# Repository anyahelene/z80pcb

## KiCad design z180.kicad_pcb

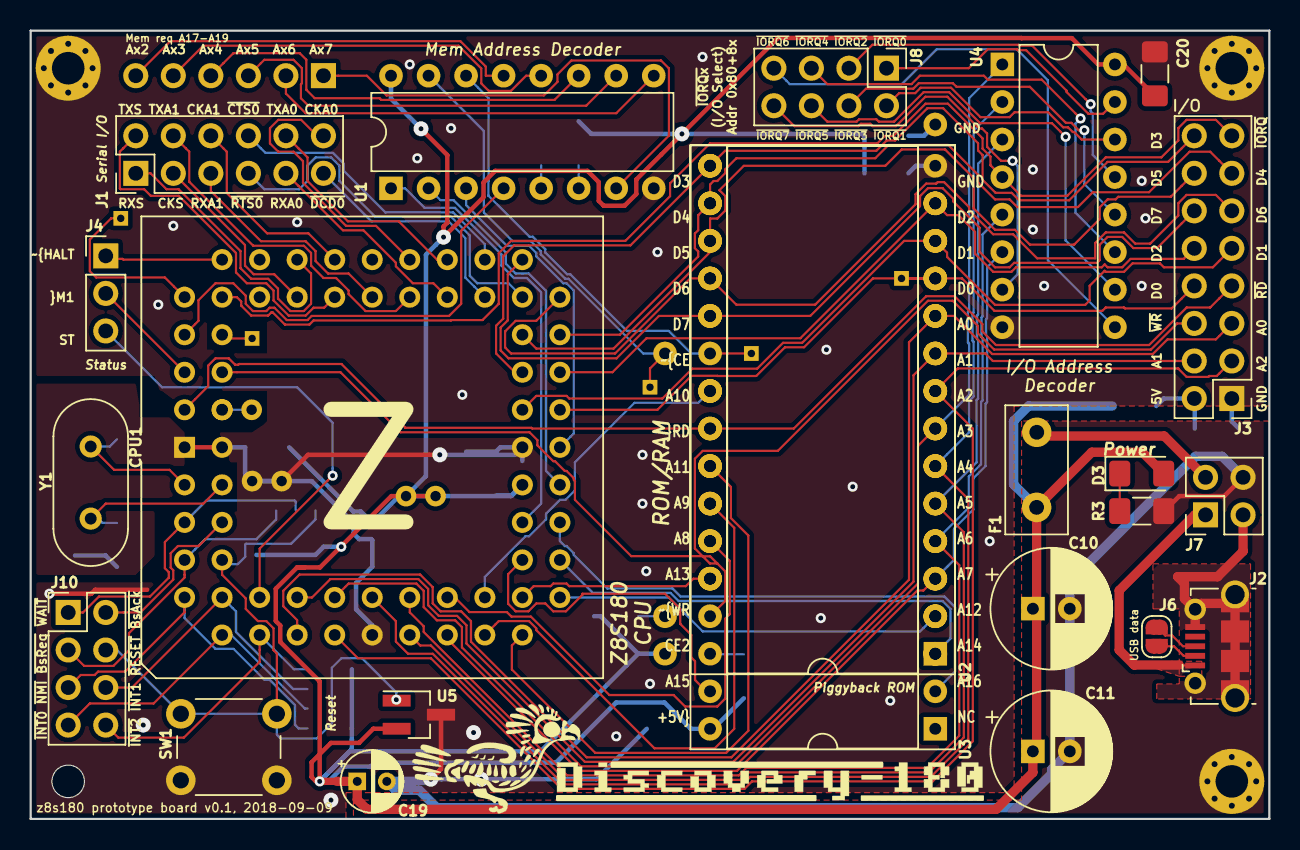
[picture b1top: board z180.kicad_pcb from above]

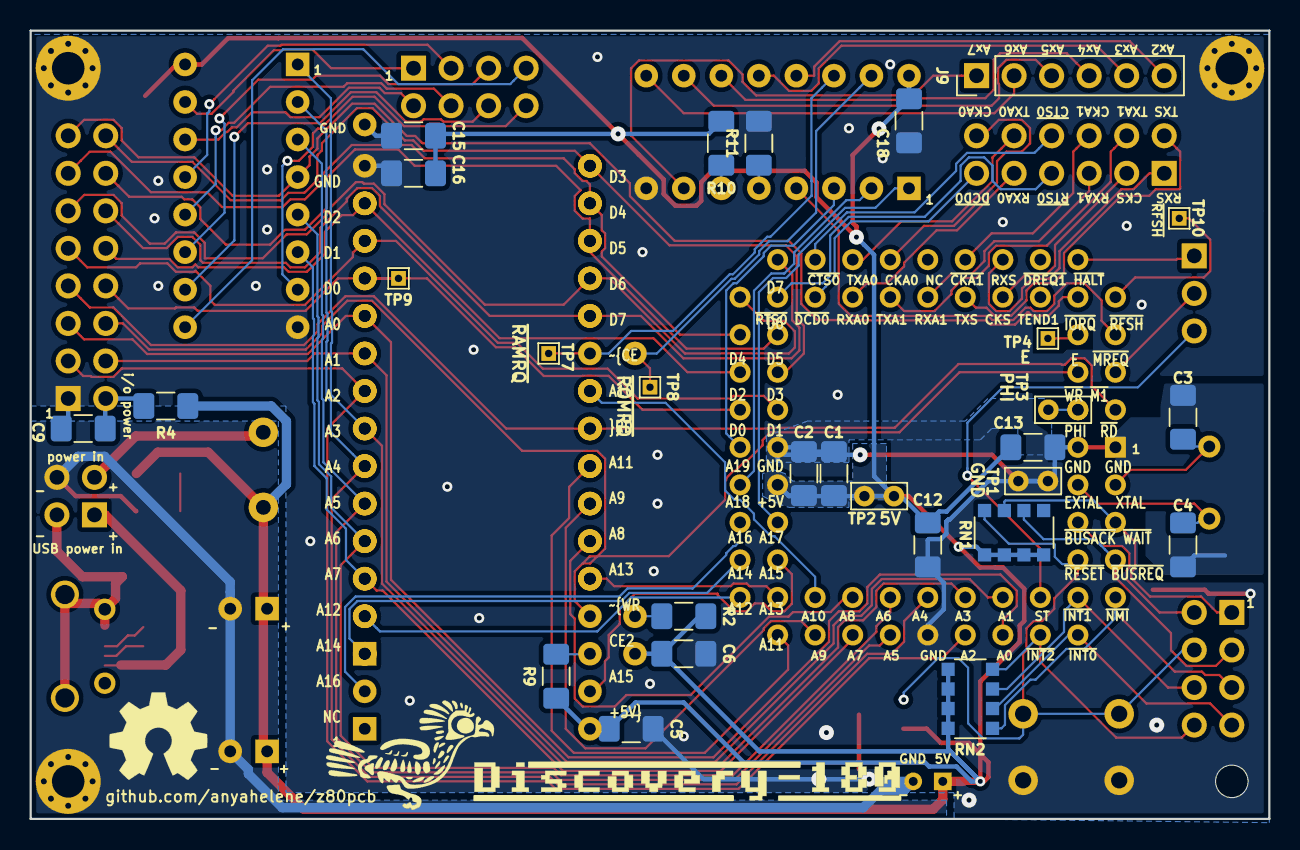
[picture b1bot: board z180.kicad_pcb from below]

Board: 2 copper layers, 83.8 x 53.3 mm, 62 parts (32 on the bottom side), 91 nets.

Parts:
C1, C5, C6, C9, C12, C13, C15, C16, C18, C20: 0.1µF; C_1206_3216Metric_Pad1.42x1.75mm_HandSolder
C2: 0.01µF; C_1206_3216Metric_Pad1.42x1.75mm_HandSolder
C3, C4: 22pF; C_1206_3216Metric_Pad1.42x1.75mm_HandSolder
C10: 10µF; CP_Radial_D8.0mm_P2.50mm
C11: 1µF; CP_Radial_D8.0mm_P2.50mm
C19: 1µF; CP_Radial_D4.0mm_P2.00mm
CPU1: Z8S180; PLCC-68_THT-Socket
D3: PWR_LED; LED_1206_3216Metric_Pad1.42x1.75mm_HandSolder
F1: 650mA; Fuse_Littlefuse_395Series
J1: SERIAL_IO; PinHeader_2x06_P2.54mm_Vertical
J2: USB Micro-B 105017; USB_Micro-B_Molex-105017-0001
J3: zdbus; PinHeader_2x08_P2.54mm_Vertical
J4: STATUS; PinHeader_1x03_P2.54mm_Vertical
J6: USB_DATA; SolderJumper-2_P1.3mm_Open_RoundedPad1.0x1.5mm
J7: POWER_IN; PinHeader_2x02_P2.54mm_Vertical
J8: Conn_01x08; PinHeader_2x04_P2.54mm_Vertical
J9: MEM_ADDR; PinHeader_1x06_P2.54mm_Vertical
J10: BUSCTRL; PinHeader_2x04_P2.54mm_Vertical
JP1, JP2: SolderJumper_2_Bridged; NetTie-2_SMD_Pad0.5mm
MH1, MH3, MH4: M2; MountingHole_2.2mm_M2_Pad_Via
MH2: M2; MountingHole_2.2mm_M2
R2, R9, R10, R11: 10k; R_1206_3216Metric_Pad1.42x1.75mm_HandSolder
R3: 330R; R_1206_3216Metric_Pad1.42x1.75mm_HandSolder
R4: 22R; R_1206_3216Metric_Pad1.42x1.75mm_HandSolder
RN1, RN2: 10k x4; R_Array_Convex_4x1206
SW1: SW_Push; SW_PUSH_6mm
TP1: TST_CPU_GND; TestPoint_Bridge_Pitch2.0mm_Drill0.7mm
TP2: TST_CPU_VCC; TestPoint_Bridge_Pitch2.0mm_Drill0.7mm
TP3: TST_PHI; TestPoint_Bridge_Pitch2.0mm_Drill0.7mm
TP4: TST_E; TestPoint_THTPad_1.0x1.0mm_Drill0.5mm
TP7: TST_RAMRQ; TestPoint_THTPad_1.0x1.0mm_Drill0.5mm
TP8: TST_ROMRQ; TestPoint_THTPad_1.0x1.0mm_Drill0.5mm
TP9: TST_D0; TestPoint_THTPad_1.0x1.0mm_Drill0.5mm
TP10: TST_RFSH; TestPoint_THTPad_1.0x1.0mm_Drill0.5mm
U1, U4: 74HCT138; DIP-16_W7.62mm
U2: 28C256; DIP-28_Piggyback_Memory_W15.24mm_Socket
U3: AS6C1008-55PCN; DIP-32_W15.24mm_Socket
U5: DS1813; SOT-23_Handsoldering
Y1: Crystal; Crystal_HC49-U_Vertical
bird1: bird_logo; bird
bird1#2: SYM_Flash_Small; bird
discovery1: discovery_logo; discovery
discovery1#2: SYM_Flash_Small; discovery
oshw1: Logo_Open_Hardware_Small; OSHW-Symbol_6.7x6mm_SilkScreen

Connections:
+5V: C1.1, C2.1, C5.1, C6.1, C12.2, C13.2, C15.2, C16.2, C18.2, C20.1, CPU1.34, JP1.2, R2.1, R9.1, R10.1, RN1.5, RN1.6, RN1.7, RN1.8, RN2.1, RN2.2, RN2.3, RN2.4, TP2.1, U1.16, U2.28, U3.32, U4.16, U5.2
/A0: CPU1.14, J3.5, U2.10, U3.12
/A1: CPU1.15, J3.4, U2.9, U3.11
/A2: CPU1.16, J3.3, U2.8, U3.10
/A3: CPU1.17, U2.7, U3.9, U4.1
/A4: CPU1.19, U2.6, U3.8, U4.2
/A5: CPU1.20, U2.5, U3.7, U4.3
/A6: CPU1.21, U2.4, U3.6, U4.5
/A7: CPU1.22, U2.3, U3.5, U4.6
/A8: CPU1.23, U2.25, U3.27
/A9: CPU1.24, U2.24, U3.26
/A10: CPU1.25, U2.21, U3.23
/A11: CPU1.26, U2.23, U3.25
/A12: CPU1.27, U2.2, U3.4
/A13: CPU1.28, U2.26, U3.28
/A14: CPU1.29, U2.1, U3.3
/A15: CPU1.30, U3.31
/A16: CPU1.31, U3.2
/A17: CPU1.32, U1.1
/A18: CPU1.33, U1.2
/A19: CPU1.35, U1.3
/CE2: R9.2, U3.30
/CKA0: CPU1.50, J1.12
/CKA1: CPU1.54, J1.6
/CKS: CPU1.57, J1.3
/D0: CPU1.37, J3.8, TP9.1, U2.11, U3.13
/D1: CPU1.38, J3.9, U2.12, U3.14
/D2: CPU1.39, J3.10, U2.13, U3.15
/D3: CPU1.40, J3.16, U2.15, U3.17
/D4: CPU1.41, J3.13, U2.16, U3.18
/D5: CPU1.42, J3.14, U2.17, U3.19
/D6: CPU1.43, J3.11, U2.18, U3.20
/D7: CPU1.44, J3.12, U2.19, U3.21
/E: CPU1.64, TP4.1
/EXTAL: C4.1, CPU1.4, Y1.1
/G1: R10.2, U1.6
/IO_5V: C9.1, J3.2, R4.2
/PHI: CPU1.68, TP3.1
/PWRIN_5V: F1.2, J7.2
/PWRIN_GND: C10.2, C11.2, C19.2, J7.4, JP2.1, MH1.1, R3.2
/REG_5V: C10.1, C11.1, C19.1, D3.2, F1.1, JP1.1, R4.1
/RXA0: CPU1.49, J1.9
/RXA1: CPU1.53, J1.5
/RXS: CPU1.56, J1.1
/ST: CPU1.13, J4.3
/TXA0: CPU1.48, J1.10
/TXA1: CPU1.51, J1.4
/TXS: CPU1.55, J1.2
/USB_DM: J2.2, J6.2
/USB_DP: J2.3, J6.1
/USB_GND: J2.5, J2.6, J7.3
/USB_Vbus: J2.1, J7.1
/XTAL: C3.1, CPU1.3, Y1.2
/~Ax2: J9.6, U1.13
/~Ax3: J9.5, U1.12
/~Ax4: J9.4, U1.11
/~Ax5: J9.3, U1.10
/~Ax6: J9.2, U1.9
/~Ax7: J9.1, U1.7
/~BUSACK: CPU1.6, J10.2
/~BUSREQ: CPU1.7, J10.3, RN1.2
/~CTS0: CPU1.46, J1.8
/~DCD0: CPU1.47, J1.11
/~EEWR: R2.2, U2.27
/~G2B: R11.1, U1.5
/~HALT: CPU1.60, J4.1
/~INT0: CPU1.10, J10.7, RN2.6
/~INT1: CPU1.11, J10.6, RN2.7
/~INT2: CPU1.12, J10.8, RN2.8
/~IORQ: CPU1.62, J3.15, U4.4
/~IORQ0: J8.1, U4.15
/~IORQ1: J8.2, U4.14
/~IORQ2: J8.3, U4.13
/~IORQ3: J8.4, U4.12
/~IORQ4: J8.5, U4.11
/~IORQ5: J8.6, U4.10
/~IORQ6: J8.7, U4.9
/~IORQ7: J8.8, U4.7
/~M1: CPU1.65, J4.2
/~MREQ: CPU1.63, U1.4
/~NMI: CPU1.9, J10.5, RN2.5
/~RAMRQ: TP7.1, U1.14, U3.22
/~RD: CPU1.67, J3.7, U2.22, U3.24
/~RESET: CPU1.8, J10.4, RN1.4, SW1.1, U5.1
/~RFSH: CPU1.61, TP10.1
/~ROMRQ: TP8.1, U1.15, U2.20
/~RTS0: CPU1.45, J1.7
/~WAIT: CPU1.5, J10.1, RN1.3
/~WR: CPU1.66, J3.6, U3.29
Earth: C1.2, C2.2, C3.2, C4.2, C5.2, C6.2, C9.2, C12.1, C13.1, C15.1, C16.1, C18.1, C20.2, CPU1.1, CPU1.2, CPU1.18, CPU1.36, J3.1, JP2.2, MH2.1, MH3.1, MH4.1, R11.2, SW1.2, TP1.1, U1.8, U2.14, U3.16, U4.8, U5.3
unnamed: D3.1, R3.1

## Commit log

2018-09-08 initial import
2018-09-09 layout mostly complete
2018-09-09 add logo
2018-09-09 final for v0.1
